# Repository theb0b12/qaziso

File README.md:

# QazIso

> [!NOTE]
> The pcb section is not finished / I probably won't complete the PCB for this project. They are just there because I made them, and maybe at somepoint someone would want to finish it. The schematic is finished if people want to look at that to base a project off of.

## Features
- 34 keys
- 6.25u spacebar
- qaz style leftmost column
- ISO Enter key!!
- handwired (my build)
- 10.25u
- Case
    - 5° uptilt
    - 3mm thick walls
    - minimalist

Cool photos here...

[My zmk config](https://github.com/theb0b12/zmk-config-qaziso)

## Handwiring Guide

## KLE
The KLE(keyboard layout editor) files are in the kle folder. There is also a 10u version with the small iso enter key. This is a lot like the TEAQAZ from dashkeebs. And then v3 is just something else that probably should never be made...

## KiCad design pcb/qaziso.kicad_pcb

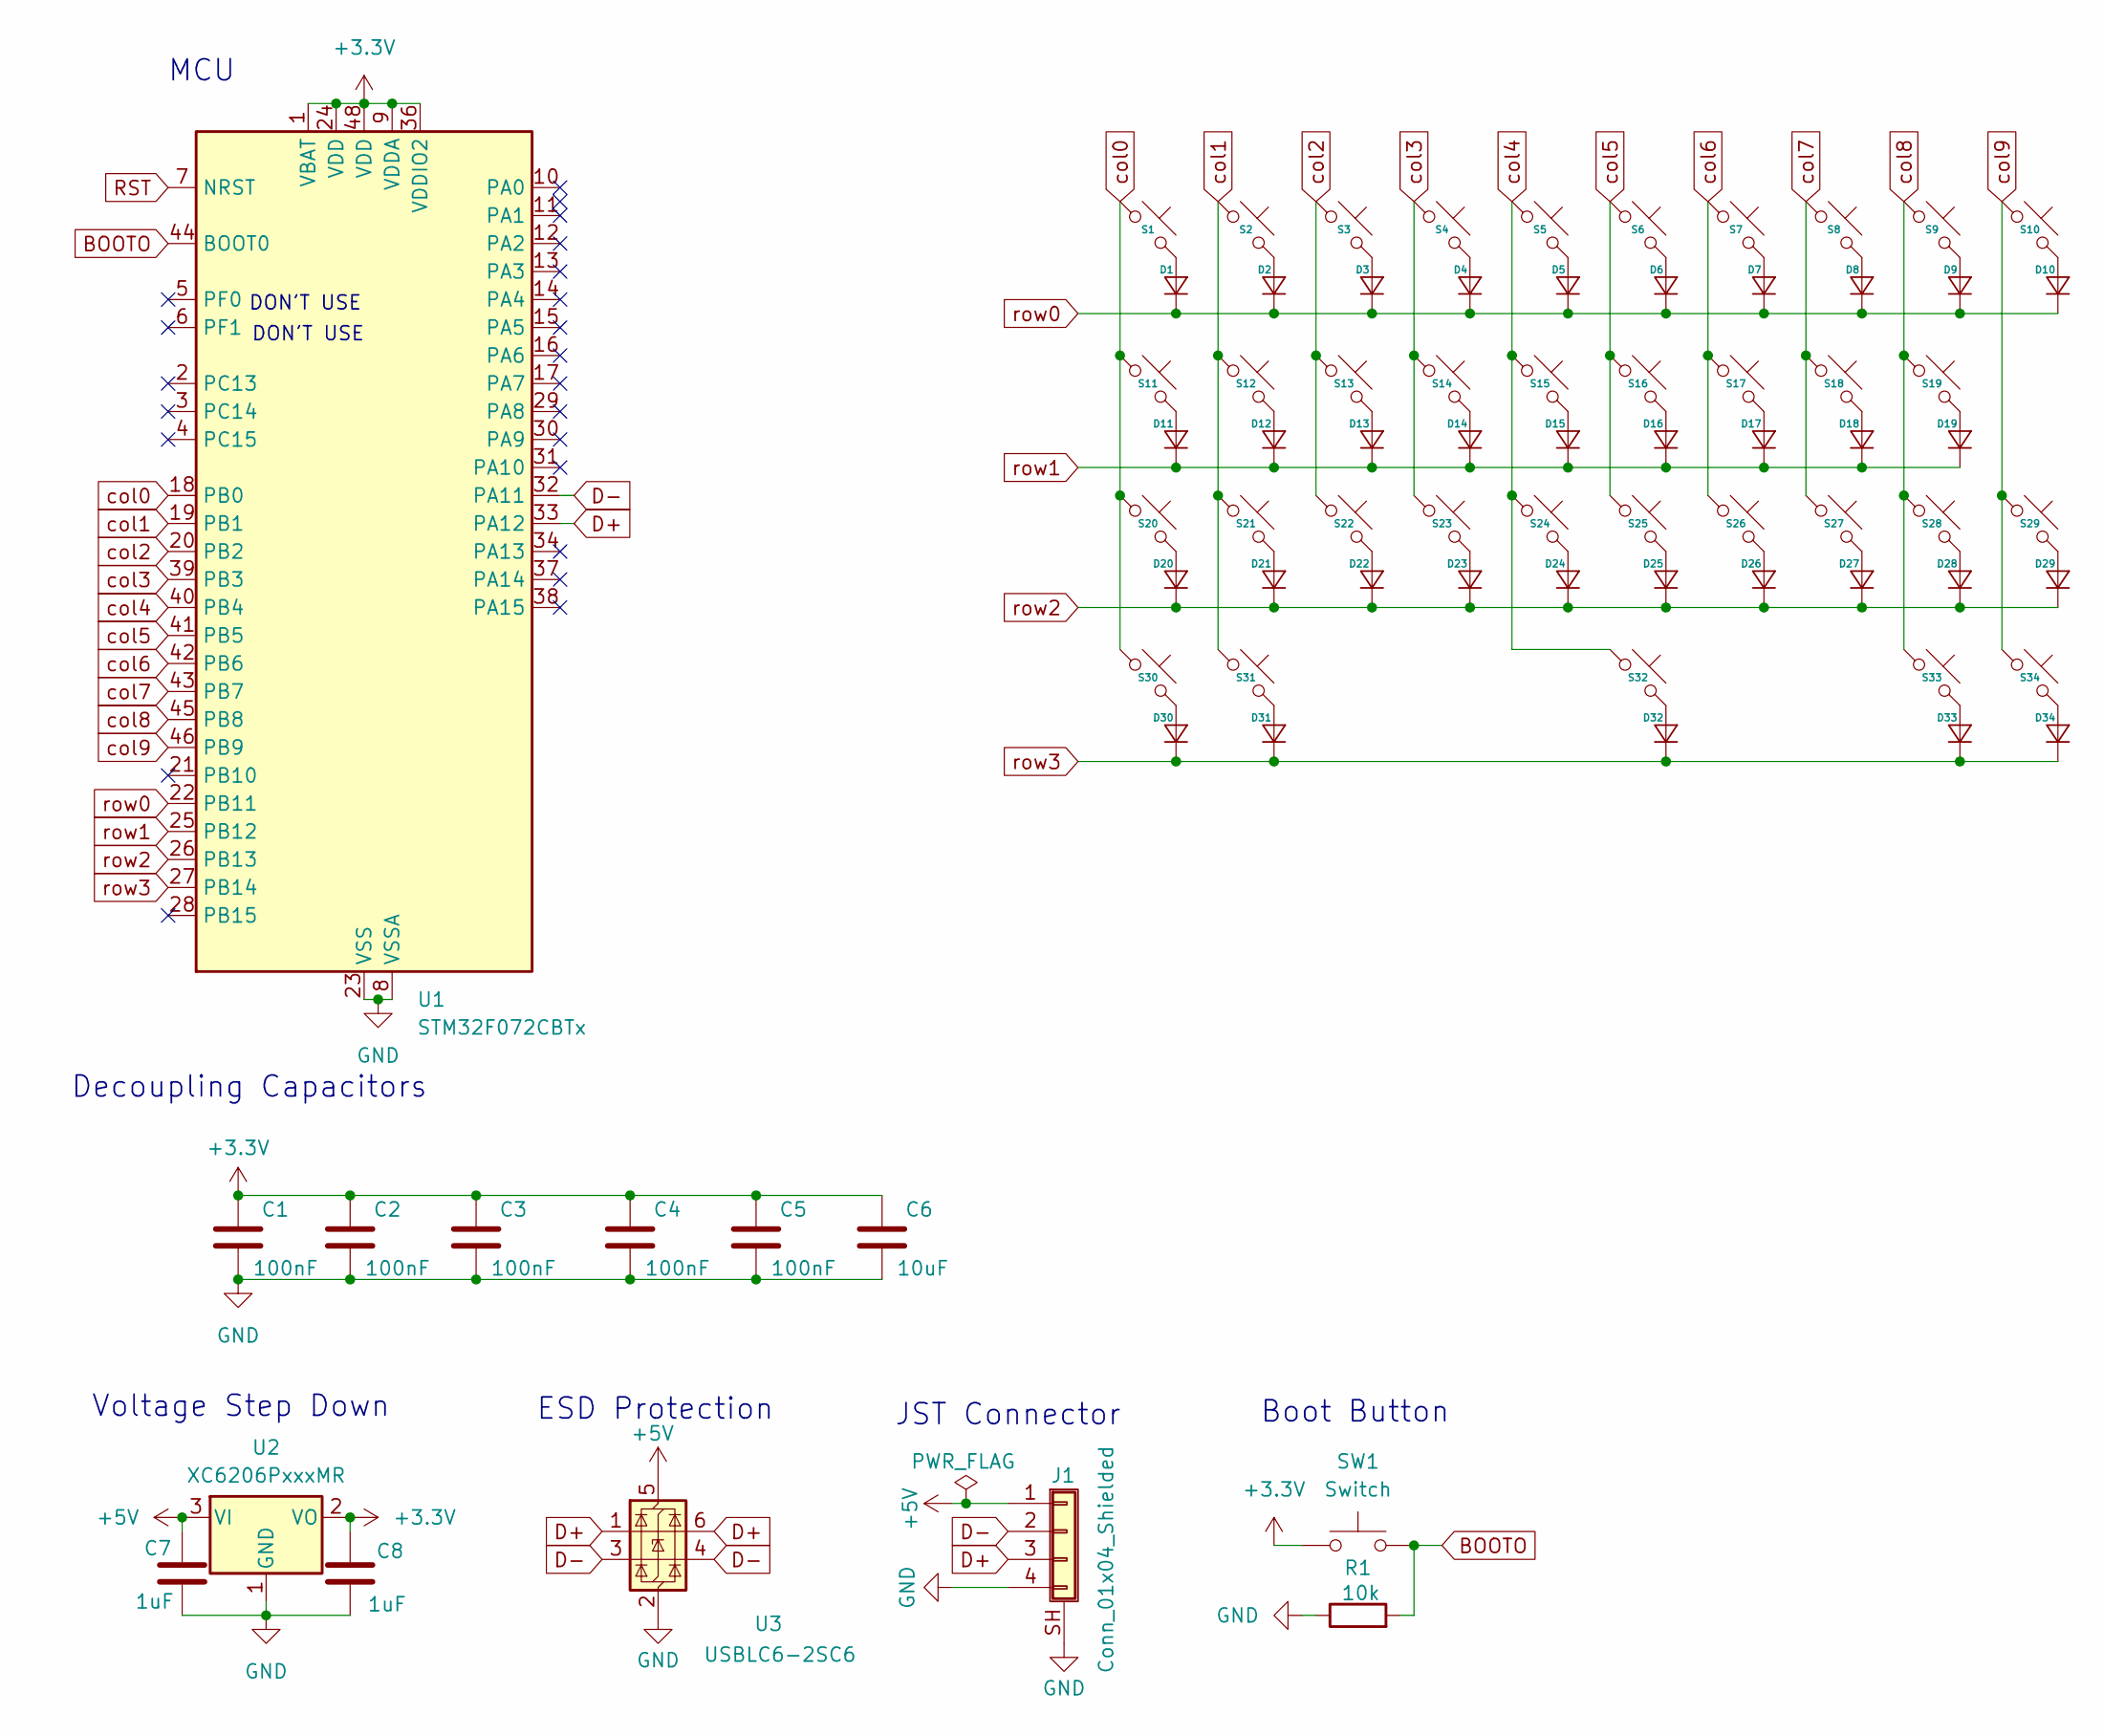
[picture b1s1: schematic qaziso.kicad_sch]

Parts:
C1: 100nF; C_0603_1608Metric; LCSC # C49678
C2, C3, C4, C5: 100nF; C_0603_1608Metric
C6: 10uF; C_0603_1608Metric
C7, C8: 1uF; C_0603_1608Metric
D1, D2, D3, D4, D5, D6, D7, D8, D9, D10, D11, D12, D13, D14, D15, D16, D17, D18, D19, D20, D21, D22, D23, D24, D25, D26, D27, D28, D29, D30, D31, D32, D33, D34: D_0603_1608Metric
J1: Conn_01x04_Shielded; JST_SH_SM04B-SRSS-TB_1x04-1MP_P1.00mm_Horizontal
R1: 10k; R_0603_1608Metric
S1, S2, S3, S4, S5, S6, S7, S8, S9, S12, S13, S14, S15, S16, S17, S18, S19, S21, S22, S23, S24, S25, S26, S27, S28, S29, S30, S31, S33, S34: Hotswap_MX_1.00u
S10: Hotswap_MX_ISOEnter
S11: Hotswap_MX_1.25u
S20: Hotswap_MX_1.50u
S32: Hotswap_MX_6.50u
SW1: Switch; SW_SKQGAFE010
U1: STM32F072CBTx; QFP50P900X900X160-48N
U2: XC6206PxxxMR; SOT-23-3
U3: USBLC6-2SC6; SOT-23-6

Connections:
+3.3V: C1.1, C2.1, C3.1, C4.1, C5.1, C6.1, C8.1, SW1.1, U1.1 (VBAT), U1.9 (VDDA), U1.24 (VDD), U1.36 (VDDIO2), U1.48 (VDD), U2.2 (VO)
+5V: C7.1, J1.1, U2.3 (VI), U3.5 (VBUS)
BOOTO: R1.2, SW1.2, U1.44 (BOOT0)
D+: J1.3, U1.33 (PA12), U3.1 (I/O1), U3.6 (I/O1)
D-: J1.2, U1.32 (PA11), U3.3 (I/O2), U3.4 (I/O2)
GND: C1.2, C2.2, C3.2, C4.2, C5.2, C6.2, C7.2, C8.2, J1.4, J1.SH (Shield), R1.1, U1.8 (VSSA), U1.23 (VSS), U1.35 (VSS), U1.47 (VSS), U2.1 (GND), U3.2 (GND)
unnamed: D1.2 (A), S1.2
unnamed: D2.2 (A), S2.2
unnamed: D3.2 (A), S3.2
unnamed: D4.2 (A), S4.2
unnamed: D5.2 (A), S5.2
unnamed: D6.2 (A), S6.2
unnamed: D7.2 (A), S7.2
unnamed: D8.2 (A), S8.2
unnamed: D9.2 (A), S9.2
unnamed: D10.2 (A), S10.2
unnamed: D11.2 (A), S11.2
unnamed: D12.2 (A), S12.2
unnamed: D13.2 (A), S13.2
unnamed: D14.2 (A), S14.2
unnamed: D15.2 (A), S15.2
unnamed: D16.2 (A), S16.2
unnamed: D17.2 (A), S17.2
unnamed: D18.2 (A), S18.2
unnamed: D19.2 (A), S19.2
unnamed: D20.2 (A), S20.2
unnamed: D21.2 (A), S21.2
unnamed: D22.2 (A), S22.2
unnamed: D23.2 (A), S23.2
unnamed: D24.2 (A), S24.2
unnamed: D25.2 (A), S25.2
unnamed: D26.2 (A), S26.2
unnamed: D27.2 (A), S27.2
unnamed: D28.2 (A), S28.2
unnamed: D29.2 (A), S29.2
unnamed: D30.2 (A), S30.2
unnamed: D31.2 (A), S31.2
unnamed: D32.2 (A), S32.2
unnamed: D33.2 (A), S33.2
unnamed: D34.2 (A), S34.2
RST: U1.7 (NRST)
col0: S1.1, S11.1, S20.1, S30.1, U1.18 (PB0)
col1: S2.1, S12.1, S21.1, S31.1, U1.19 (PB1)
col2: S3.1, S13.1, S22.1, U1.20 (PB2)
col3: S4.1, S14.1, S23.1, U1.39 (PB3)
col4: S5.1, S15.1, S24.1, S32.1, U1.40 (PB4)
col5: S6.1, S16.1, S25.1, U1.41 (PB5)
col6: S7.1, S17.1, S26.1, U1.42 (PB6)
col7: S8.1, S18.1, S27.1, U1.43 (PB7)
col8: S9.1, S19.1, S28.1, S33.1, U1.45 (PB8)
col9: S10.1, S29.1, S34.1, U1.46 (PB9)
row0: D1.1 (K), D2.1 (K), D3.1 (K), D4.1 (K), D5.1 (K), D6.1 (K), D7.1 (K), D8.1 (K), D9.1 (K), D10.1 (K), U1.22 (PB11)
row1: D11.1 (K), D12.1 (K), D13.1 (K), D14.1 (K), D15.1 (K), D16.1 (K), D17.1 (K), D18.1 (K), D19.1 (K), U1.25 (PB12)
row2: D20.1 (K), D21.1 (K), D22.1 (K), D23.1 (K), D24.1 (K), D25.1 (K), D26.1 (K), D27.1 (K), D28.1 (K), D29.1 (K), U1.26 (PB13)
row3: D30.1 (K), D31.1 (K), D32.1 (K), D33.1 (K), D34.1 (K), U1.27 (PB14)

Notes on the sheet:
JST Connector
DON'T USE
Voltage Step Down
Decoupling Capacitors
MCU
Boot Button
ESD Protection

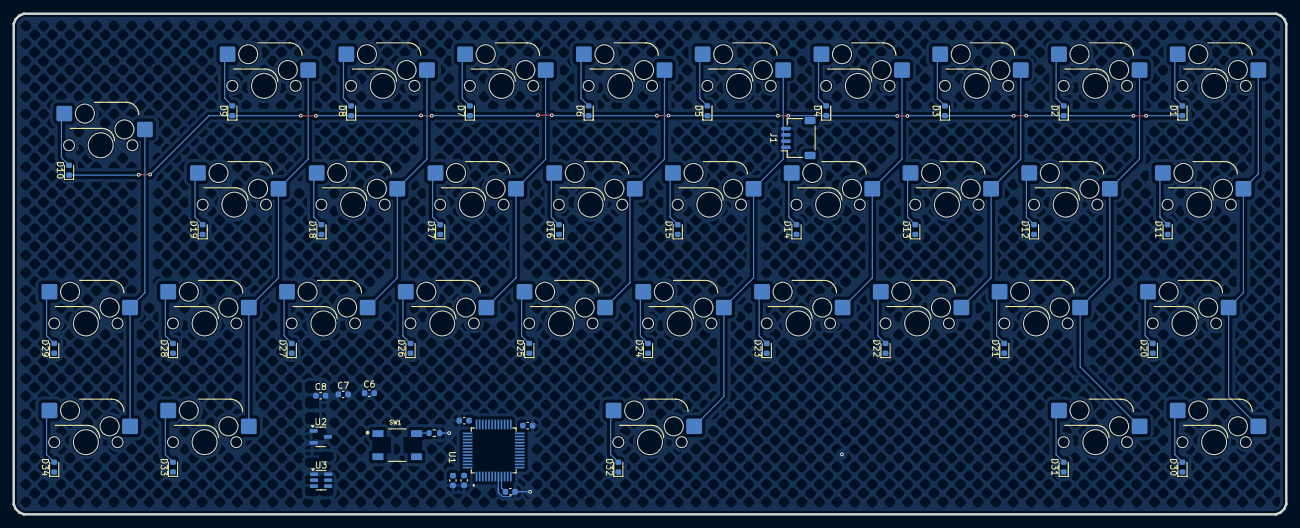
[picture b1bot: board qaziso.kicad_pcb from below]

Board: 2 copper layers, 204.1 x 80.3 mm, 82 parts (48 on the bottom side), 54 nets.
